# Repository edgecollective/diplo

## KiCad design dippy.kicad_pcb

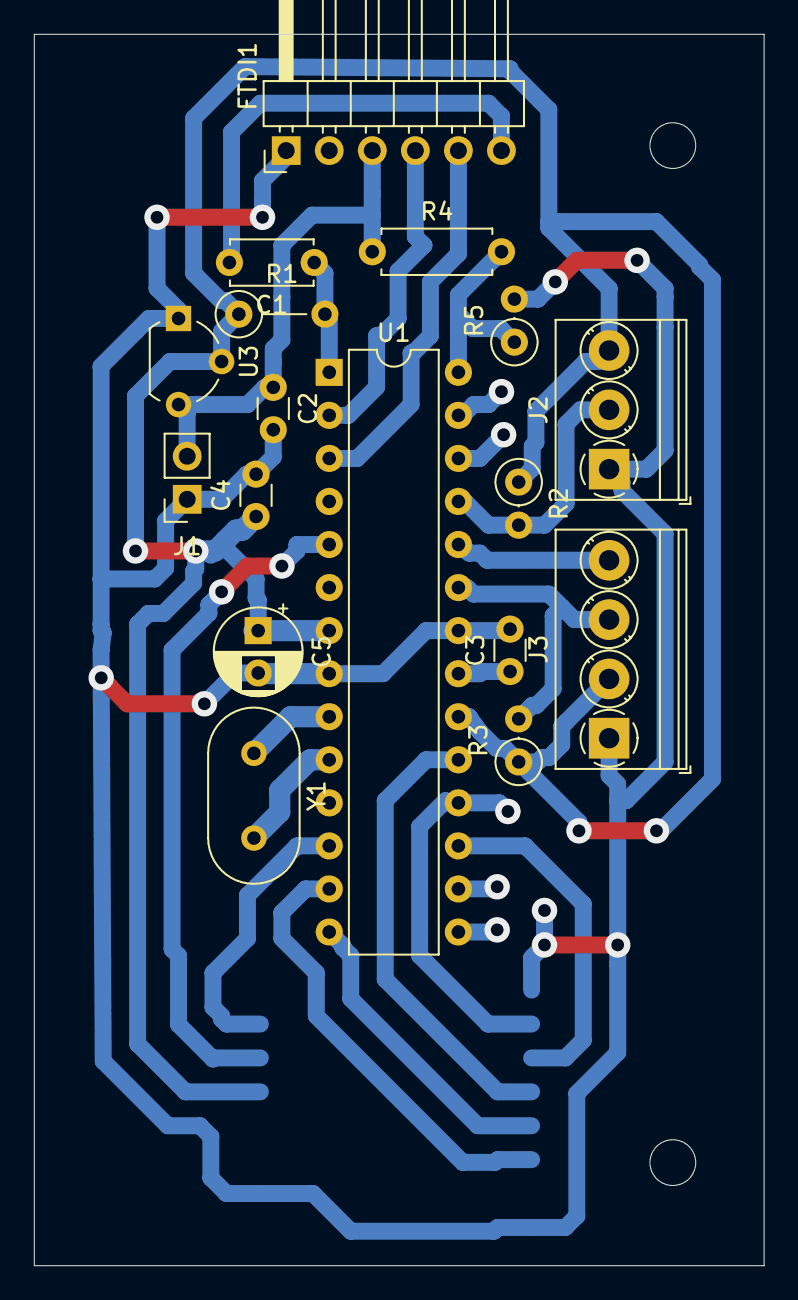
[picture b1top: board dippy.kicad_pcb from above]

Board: 2 copper layers, 43.1 x 72.6 mm, 20 parts (1 on the bottom side), 21 nets.

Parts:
C1: 0.1u; C_Disc_D4.7mm_W2.5mm_P5.00mm
C2, C3, C4: 0.1u; C_Disc_D3.0mm_W1.6mm_P2.50mm
C5: 10u; CP_Radial_D5.0mm_P2.50mm
FTDI1: Conn_01x06_Male; PinHeader_1x06_P2.54mm_Horizontal
H2, H4: MountingHole; MountingHole_2.7mm_M2.5
J1: Conn_01x02_Female; PinSocket_1x02_P2.54mm_Vertical
J2: Screw_Terminal_01x03; TerminalBlock_Phoenix_PT-1,5-3-3.5-H_1x03_P3.50mm_Horizontal
J3: Screw_Terminal_01x04; TerminalBlock_Phoenix_PT-1,5-4-3.5-H_1x04_P3.50mm_Horizontal
R1: 10K; R_Axial_DIN0207_L6.3mm_D2.5mm_P5.08mm_Vertical
R2, R3: 10K; R_Axial_DIN0207_L6.3mm_D2.5mm_P2.54mm_Vertical
R4: 100K; R_Axial_DIN0207_L6.3mm_D2.5mm_P7.62mm_Horizontal
R5: 100K; R_Axial_DIN0207_L6.3mm_D2.5mm_P2.54mm_Vertical
U1: ATmega328P-PU-C; DIP-28_W7.62mm
U2: RFM95W-915S2; RFM95
U3: MCP1700-3302E_SOT23; TO-92L_Wide
Y1: Crystal; Resonator-2Pin_W10.0mm_H5.0mm

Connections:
A0: J3.3, R3.2, U1.23
A1: J3.4, U1.24
A2: J2.2, R2.2, U1.25
A5: R4.2, R5.1, U1.28
D3: U1.5, U2.14
D6: U1.12, U2.15
D7: U1.13, U2.6
D8: U1.14, U2.5
GND: C2.2, C3.2, C4.2, C5.2, FTDI1.1, J1.1, J2.1, J3.1, R5.2, U1.8, U1.22, U2.1, U2.8, U2.10, U3.1
MISO: U1.18, U2.2
MOSI: U1.17, U2.3
unnamed: C1.1, R1.2, U1.1
unnamed: C1.2, FTDI1.6
unnamed: C3.1, U1.21
unnamed: U1.9, Y1.1
unnamed: U1.10, Y1.2
RX0: FTDI1.4, U1.2
SCK: U1.19, U2.4
TX0: FTDI1.5, U1.3
VCC: C4.1, C5.1, J2.3, J3.2, R1.1, R2.1, R3.1, U1.7, U1.20, U2.13, U3.2
VIN: C2.1, FTDI1.3, J1.2, R4.1, U3.3
